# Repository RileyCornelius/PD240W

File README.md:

# PD240W

An adjustable power supply for motor drives using USB-C Power Delivery negotiation, supporting up to **240W at 48V 5A**. This device is designed to be compatible with USB-PD up to 3.2. Firmware runs on a Raspberry Pi Pico ([RP2040](https://www.raspberrypi.com/products/rp2040/)).

> [!NOTE]
> This is a fork of [theohg/PD240W](https://github.com/theohg/PD240W) by Théo Heng. The board, enclosure and firmware build differ from the original. See [Fork Changes](#fork-changes).

Follow the original project's logs and updates on <a href="https://hackaday.io/project/205084-pd240w" target="_blank" title="PD240W on Hackaday.io">
Hackaday.io 
</a>

> [!WARNING]
> **Disclaimer**: Firmware v2.0.0 includes guarded AVS/EPR negotiation, startup restore, and EPR-exit handling, but high-voltage charger interoperability still depends on the source and cable combination you test with. Validate 28V/36V/48V operation on your hardware.

## Table of Contents

- [Fork Changes](#fork-changes)
- [Features](#features)
- [Hardware](#hardware)
- [Quick Start](#quick-start)
- [Controls](#controls)
- [Firmware Structure](#firmware-structure)
- [Want one?](#want-one)
- [Planned Features](#planned-features)
- [Acknowledgements](#acknowledgements)

## Fork Changes

This fork makes these changes to the [original project](https://github.com/theohg/PD240W):

- **5V regulator instead of 17V**: The auxiliary buck regulator (LMR16006X) now outputs 5V instead of the original 17V. Its feedback divider, inductor (now 33µH) and output capacitor (now 22µF 25V) were changed to suit. Firmware v2.1.0 labels the output "5V" and allows it to be enabled when VBUS is 7V or higher (the original required 18V).
- **Top case exposes the whole terminal block**: `casing_top` was modified so the entire output terminal block is uncovered.
- **Enclosure recreated in SolidWorks**: The enclosure is now modeled in SolidWorks, in `mechanical/solidworks/`.
- **Production files for the modified board**: The JLCPCB order files are in `hardware/production/`. The KiBot documentation package in `hardware/Manufacturing/` and the schematic PDF were regenerated for hardware revision 1.1.0. See [hardware/README.md](hardware/README.md#production-files).
- **PlatformIO firmware build**: The firmware builds with PlatformIO from `firmware/` and replaces the original CMake / Pico SDK build. See [Build from Source](#build-from-source).

## Features

- **USB-C Power Delivery**: Negotiates Fixed, PPS (3.3-21V programmable), and AVS (15-48V EPR) profiles
- **Current Limiting**: Adjustable 10mA-5A via INA228 power monitor with hardware overcurrent protection
- **LCD Interface**: 240x320 ST7789 display with anti-aliased fonts and Prusa-style encoder navigation
- **Safety**: Overcurrent ISR, overtemperature monitoring (NTC + INA228)
- **Settings Persistence**: User settings stored in RP2040 flash with CRC32 validation
- **Auto PPS/AVS Tuning**: Closed-loop voltage correction for PPS/AVS charger output accuracy
- **Charger Diagnostics**: On-device PD revision, charger identity, cable inference, and max-power reporting
- **Remote CLI**: USB serial command interface for measurements, PD selection, and settings updates
- **Energy Monitoring**: Tracks mAh delivered since boot via INA228 charge accumulator
- **5V Buck Output**: Optional auxiliary 5V output (17V mock STO/SBC voltage on the original board)
- **Configurable**: Brightness, auto-dim, startup melody, auto-output on boot and more

## Hardware

| Type | Path | Contents |
|------|------|----------|
| PCB (KiCad) | `hardware/` | Schematics and PCB layout |
| PCB (STEP) | `mechanical/PD240W_PCB.stp` | Full PCB 3D model |
| Enclosure (SolidWorks) | `mechanical/solidworks/` | Enclosure assembly and part files |
| Enclosure (STEP) | `mechanical/solidworks/STEP/` | Casing top/bottom, knob, button, LCD support, SWD cover |
| Schematic (PDF) | `hardware/Schematic/` | Schematic for hardware revision 1.1.0 |
| JLCPCB order files | `hardware/production/` | Gerbers zip, BOM, pick and place for JLCPCB |
| Gerbers | `hardware/Manufacturing/Fabrication/` | Gerbers, drill files, ODB++, fabrication drawing |
| BOM | `hardware/Manufacturing/Assembly/` | Bill of materials (CSV, HTML, interactive) |
| Pick & Place | `hardware/Manufacturing/Assembly/` | Pick and place file, assembly drawing |

### Hardware Errata

USB data lines (D+/D-) are reversed in the current PCB revision (1.1.0), preventing native USB communication between the RP2040 and the USB host. This can be easily fixed by crossing the D+ and D- lines on the PCB by crossing the series 27Ω resistors as shown below:

> [!NOTE]
> **TODO**: This fork has not fixed the swapped USB data lines in the PCB layout yet.

## Quick Start

### Flash Pre-built Firmware

1. Download `PD240W.uf2` from the original project's [latest release](https://github.com/theohg/PD240W/releases/latest). This fork has no releases of its own yet.
2. Hold **BOOTSEL** button on the Pico while connecting USB
3. Drag `PD240W.uf2` to the mounted `RPI-RP2` drive

### Build from Source

Requires: [PlatformIO](https://platformio.org/) (CLI, or the VS Code extension recommended in `firmware/.vscode/extensions.json`). On the first build PlatformIO downloads the toolchain and the [Arduino-Pico](https://github.com/earlephilhower/arduino-pico) core, which bundles the Pico SDK.

```bash
git clone https://github.com/RileyCornelius/PD240W.git
cd PD240W/firmware

pio run                  # Debug build (LOG_DEBUG on)
pio run -e pico_release  # Release build (debug logging off, -Werror)
```

The output binary is `firmware/.pio/build/<env>/firmware.uf2`, where `<env>` is `pico` or `pico_release`. Release downloads rename it to `PD240W.uf2`.

The INA228 and TPS26750 drivers are copied into `firmware/lib/` from [ina228_multiplatform](https://github.com/theohg/ina228_multiplatform) and [tps26750_multiplatform](https://github.com/theohg/tps26750_multiplatform). They do not update automatically. To update one, replace its folder in `firmware/lib/` and bump the version in its `library.json` and in `firmware/src/config/version.h`.

### Run Unit Tests

The host tests cover the hardware-free logic headers and run on your PC, not the Pico. They need a host `g++` on `PATH`:

```bash
cd firmware
pio test -e native
```

See [firmware/test/README](firmware/test/README) for details.

### Flash via SWD

```bash
openocd -f interface/cmsis-dap.cfg -f target/rp2040.cfg \
  -c "adapter speed 5000; program firmware/.pio/build/pico/firmware.elf verify reset exit"
```

> [!IMPORTANT]
> **EEPROM Initial Setup**: Before full PD negotiation can work, you must flash the **TPS26750 EEPROM** configuration. This is done via the **EEPROM Flash** workflow found in the **Settings** menu. 
> 
> **Note**: Before the EEPROM is flashed, the board will only power on when connected to a standard 5V non-PD charger (USB BC1.2 mode).

Once the firmware has been successfully flashed, connect the device to a compatible USB-PD power source and interact with the encoder and buttons to navigate the menus and adjust settings as explained below.

> [!NOTE]
> Finding a compact and affordable charger supporting **USB-PD 3.1** (up to 48V EPR) is currently quite rare. Here are a few known options:
>
> | Model | Max single-port PD Output | Voltage Profile | Approx. Price |
> |---|---|---|---|
> | **[UGREEN Nexode 140W](https://fr.ugreen.com/products/ugreen-nexode-140w-chargeur-usb-c-pd-3-1-3-ports)** | 140W | 28V @ 5A | ~60€ |
> | **[Framework Power Adapter - 180W](https://frame.work/fr/fr/products/16-power-adapter?v=FRANCR000F)** | 180W | 36V @ 5A | ~109€ |
> | **[HKY 240W GaN Charger](https://www.amazon.de/-/en/Charger-Framework-Thunderbolt-External-ADP-240KB/dp/B0FLXY1HYW/ref=sr_1_2?crid=3N3IPHZQ5LLC7&dib=eyJ2IjoiMSJ9.Hby-yLg1Ti0JNivqvDzvN57zIH6zG4_c9wlyL50Z52GmOPyP_vKubcMJ3zNZ7RRcIgOo2FKgZio1hprqALfRdOTl2DQ7Dp27o4l66qmaDQw9ctSuX0EaWnDfyVwVAMaSwnUP7h1NBuraYlZnAgiljw.9cbe3P4mLf8D7-0faSCcJpKki5cfrjZLwFO-zW9XlJw&dib_tag=se&keywords=hky+240w&qid=1769454134&sprefix=hky+240w%2Caps%2C102&sr=8-2)** | 240W | 48V @ 5A | ~90€ |
> | **[Framework Power Adapter - 240W](https://frame.work/fr/fr/products/power-adapter-240w?v=FRAKMX000F)** | 240W | 48V @ 5A | ~120€ |
> | **[UGREEN NEXODE 500W](https://eu.ugreen.com/products/ugreen-nexode-500w-6-port-gan-desktop-fast-charger)** | 240W | 48V @ 5A | ~250€ |

## Controls

| Input | Action |
|-------|--------|
| Encoder Rotate | Navigate menus / Adjust values |
| Encoder Click | Confirm / Select |
| BTN1 (top) | Toggle load switch output |
| BTN2 (bottom) | Toggle 5V buck (requires VBUS ≥ 7V) |

### Menu Structure

```mermaid
graph TD
  %% Nodes
      Boot([Boot]) -->|≤2s| Main[Main Screen]
      Main -->|Error| Fault[Fault Screen]
      Fault -->|Click| Main
      
      Main <-->|Click| Menu[Main Menu]

      Menu --> Voltage[Select Voltage]
      Menu --> Current[Current Limit]
      Menu --> Settings[Settings]
      Menu --> AboutFirmware[About PD240W]
      Menu --> AboutCharger[About This Charger]
      Menu --> Back[Back]

      Voltage <-->|Select PDO| AdjV[Adjust Voltage]
      Current <-->|Set Limit| AdjC[Adjust Current]
      
      Settings --> EEPROM[Flash EEPROM]
      Settings --> Configs[Params: Brightness / Sounds / Tuning...]
      AboutFirmware --> Main
      AboutCharger --> Main
      
      %% Styling
      classDef default fill:#f9f9f9,stroke:#333,stroke-width:1px;
      classDef alert fill:#ffcccc,stroke:#cc0000,stroke-width:2px;
      class Fault alert;
```

| Menu Item | Description |
|-----------|-------------|
| Select Voltage | Fixed / PPS / AVS PDO selection |
| Current Limit | 10mA - 5A output current limit adjustment with encoder acceleration |
| Settings | EEPROM flash workflow plus tuning, startup, brightness, and sound options |
| About PD240W | Device identity, firmware build info, flash usage, and project link |
| About This Charger | Live PD revision, CC orientation, QC inference, and cable diagnostics |
| Back | Return to the main live display |

## Firmware Structure

```
firmware/
├── platformio.ini                  Build environments: pico, pico_release, native (tests)
├── lib/
│   ├── ina228_multiplatform/       INA228 power monitor driver
│   └── tps26750_multiplatform/     TPS26750 USB-PD controller driver
├── test/                           Host unit tests (doctest), one folder per suite
└── src/                            Application sources (below)

src/
├── main.cpp                        Entry point, non-blocking main event loop
│
├── hw/
│   ├── hardware.h/cpp              Hardware singleton aggregating all drivers
│   └── interrupts.h/cpp            Centralized GPIO interrupt router (RP2040 single-callback)
│
├── platform/
│   ├── arduino_compat.cpp          Routes the SDK console (printf, getchar) onto the core's UART
│   └── console.h                   Serial console bring-up (logs + CLI)
│
├── cli/                            Serial command interface (see src/cli/README.md)
│
├── config/
│   ├── board_config.h              Pin definitions (Board:: namespace)
│   ├── app_config.h                Timeouts, thresholds, limits (AppConfig:: namespace)
│   └── version.h                   Firmware & hardware version, author...
│
├── drivers/                        Low-level hardware drivers (no business logic)
│   ├── display/
│   │   ├── st7789.h/cpp            SPI LCD driver with AA font rendering
│   │   ├── aa_font.h               Anti-aliased font data structure
│   │   └── font_inter_*.h          Generated Inter font bitmaps (12/14/20/28px)
│   ├── input/
│   │   ├── rotary_enc.h/cpp        Quadrature encoder with velocity tracking
│   │   ├── button.h/cpp            Debounced button with click/long-press
│   │   └── adc_inputs.h/cpp        VBUS voltage + NTC temperature (ADC channels)
│   ├── gpio/                       SimpleIO: digital output with non-blocking blink
│   ├── buzzer/                     PWM buzzer with melody playback
│   └── rgb_led/                    SK6812 via PIO state machine
│
├── logic/                          Application logic
│   ├── state_machine.h/cpp         BOOT -> MAIN <-> MENU <-> ADJUST, FAULT handling
│   ├── safety.h/cpp                Temperature/voltage/current monitoring, fault triggers
│   ├── pd_manager.h/cpp            PD contract caching, PPS keep-alive, auto-tuning
│   ├── settings.h/cpp              Flash persistence with CRC32, debounced saves
│   ├── tps_eeprom_workflow.h/cpp   TPS26750 EEPROM compare/flash state machine
│   ├── cc_controller.h/cpp         Constant-current control via PD voltage requests
│   └── *.h (pure headers)          Host-testable logic: CC regulation, PD diagnostics,
│                                   PPS/AVS tuning, settings storage, thermal monitor
│
├── ui/
│   ├── display_manager.h/cpp       All screen rendering (boot, main, menu, adjust, fault)
│   ├── font_config.h               Central font size mapping (FONT_LARGE/MEDIUM/SMALL)
│   └── assets/pd240w_logo.h        Boot screen logo bitmap
│
├── utils/
│   ├── logging.h                   LOG_INFO/WARN/ERROR/DEBUG/CRITICAL macros
│   ├── pd_voltage.h                Shared programmable-voltage alignment helper
│   ├── tps_eeprom_loader.h/cpp     Low-level TPS26750 EEPROM read/write
│   ├── tps_patch_loader.h/cpp      Pushes the TPS26750 configuration over I2C at boot
│   └── tps26750_patch.c            TPS26750 binary configuration blob
```

## Want one?

Feel free to order assembled PCBs, flash the firmware, and test it for yourself! Manufacturing 5 assembled PCBs will cost approximately **$415**. 

The project is open for contributions. Don't hesitate to improve the code, report bugs, or suggest new features via Pull Requests and Issues!

## License and Copyright

This repository contains different types of source files, which are licensed as follows:

### 1. Hardware files (CC BY-NC 4.0)
All hardware design files in the `hardware/` directory (Schematics, PCB layout, Gerbers, BOM) and the enclosure files in the `mechanical/` directory are licensed under the **Creative Commons Attribution-NonCommercial 4.0 International License**. 

You are free to download, modify, and build this board for personal, educational, and hobbyist use. However, you may **not** use these designs for commercial purposes (such as manufacturing and selling the boards) without prior written permission.

Please see the [LICENSE.txt](./LICENSE.txt) file for full terms.

### 2. Firmware & Software (MIT License)
The firmware and software source code in this repository (the `firmware/` directory) is licensed under the **MIT License**. 

You are free to use, modify, and distribute the software component of this project. 

Please see the [LICENSE-FIRMWARE.txt](./LICENSE-FIRMWARE.txt) file for full terms.

## Planned Features

These are from the original project's roadmap and are not in this fork yet:

- **PPS battery charging in Constant Current (CC) mode**: PPS allows a fixed current mode that can be used for battery charging. This is to be tested by charging lithium-ion battery packs.
- **Improved CLI interface**: Needs more testing and polish.
- **Extended PPS and AVS Range**: Support for PPS voltages as low as 3.5V, AND SPR AVS profiles down to 9V.

## Acknowledgements

PD240W was designed by Théo Heng, who did all of the original hardware design and firmware development as the sole contributor. This fork builds on that work.

The original project was made possible by [Synapticon GmbH](https://www.synapticon.com), who funded and supported its development.

The original project drew inspiration from the work on portable USB-C PD power supplies by CentyLab on the [PocketPD](https://hackaday.io/project/194295-pocketpd-usb-c-portable-bench-power-supply) project and Alex Xia with his [ProtoV MINI](https://hackaday.io/project/204461-protov-mini-tiny-usb-c-breadboard-power-supply).

***

Originally made with ❤️ by Théo Heng. Fork maintained by Riley Cornelius.

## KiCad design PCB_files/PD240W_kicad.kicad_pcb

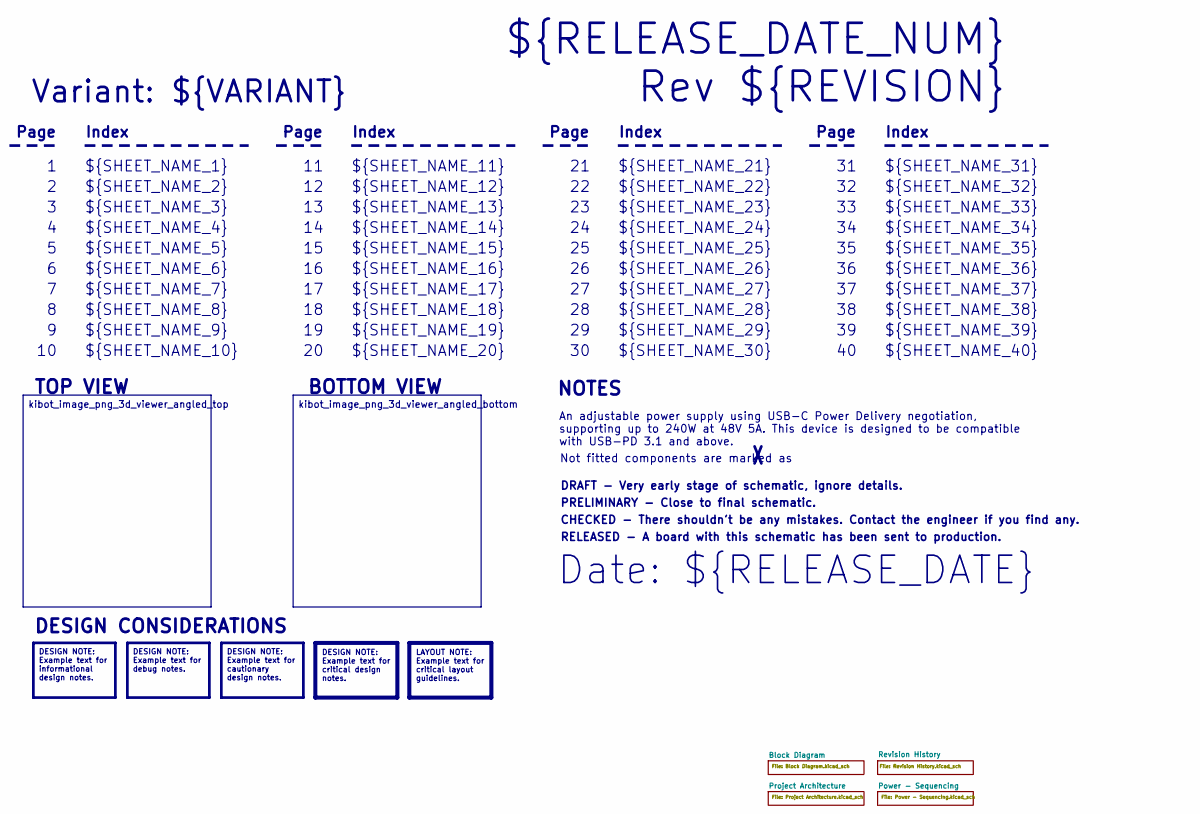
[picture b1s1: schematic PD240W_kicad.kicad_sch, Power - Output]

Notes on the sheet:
Variant: ${VARIANT}
RELEASED - A board with this schematic has been sent to production.
${SHEET_NAME_24}
Index
Page
PRELIMINARY - Close to final schematic.
${SHEET_NAME_22}
DRAFT - Very early stage of schematic, ignore details.
${SHEET_NAME_12}
${SHEET_NAME_8}
${SHEET_NAME_2}
${SHEET_NAME_5}
${SHEET_NAME_20}
${SHEET_NAME_23}
${RELEASE_DATE_NUM}
${SHEET_NAME_35}
Not fitted components are marked as
${SHEET_NAME_11}
${SHEET_NAME_6}
${SHEET_NAME_37}
${SHEET_NAME_26}
${SHEET_NAME_36}
Rev ${REVISION}
${SHEET_NAME_15}
CHECKED - There shouldn't be any mistakes. Contact the engineer if you find any.
BOTTOM VIEW
${SHEET_NAME_14}
${SHEET_NAME_21}
${SHEET_NAME_17}
${SHEET_NAME_18}
Date: ${RELEASE_DATE}
${SHEET_NAME_7}
${SHEET_NAME_31}
NOTES
${SHEET_NAME_40}
${SHEET_NAME_39}
${SHEET_NAME_32}
${SHEET_NAME_1}
${SHEET_NAME_9}
${SHEET_NAME_38}

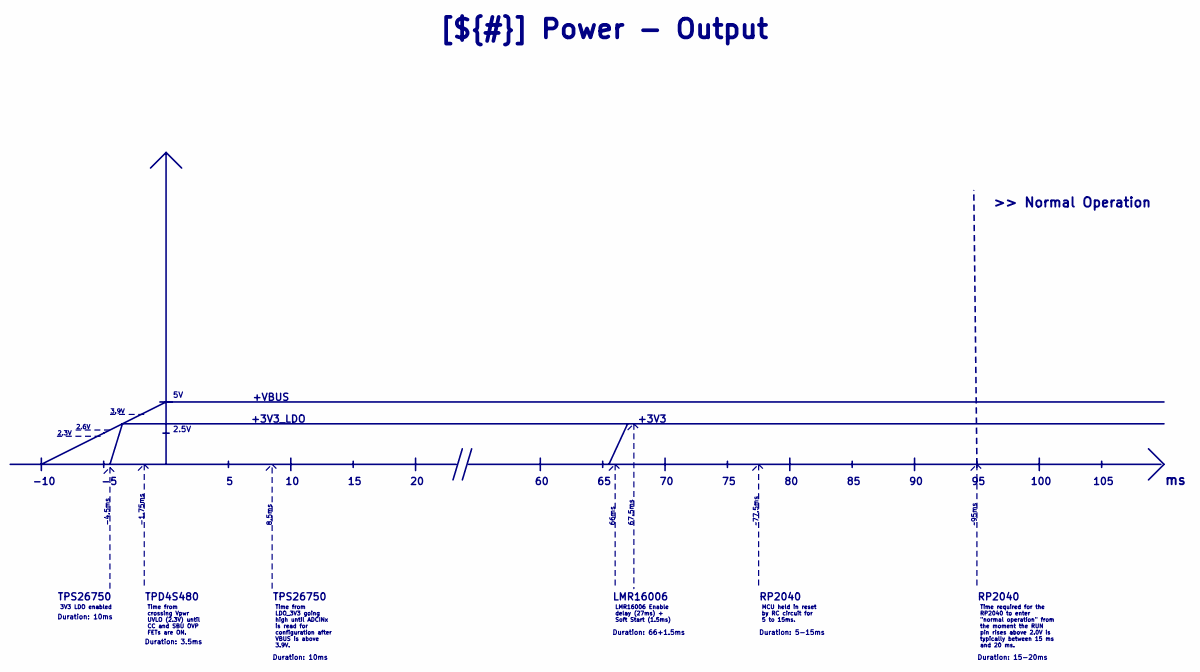
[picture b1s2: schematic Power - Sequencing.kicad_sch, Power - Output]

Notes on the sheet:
~95ms
-1.75ms
2.5V
3.9V
Duration: 15-20ms
RP2040
TPS26750
LMR16006
2.6V
+VBUS
Duration: 10ms
100
Duration: 3.5ms
Duration: 66+1.5ms
8.5ms
+3V3_LDO
66ms
67.5ms
Duration: 5-15ms
2.3V
105
~77.5ms
TPD4S480
+3V3
>> Normal Operation
-4.5ms
-10
3V3 LDO enabled
Time from LDO_3V3 going high until ADCINx is read for configuration after VBUS is above 3.9V.
Time from crossing Vpwr UVLO (2.3V) until CC and SBU OVP FETs are ON.
Time required for the RP2040 to enter "normal operation" from the moment the RUN pin rises above 2.0V is typically between 15 ms and 20 ms.
[${#}] ${TITLE}
MCU held in reset by RC circuit for 5 to 15ms.
LMR16006 Enable delay (27ms) + Soft Start (1.5ms)

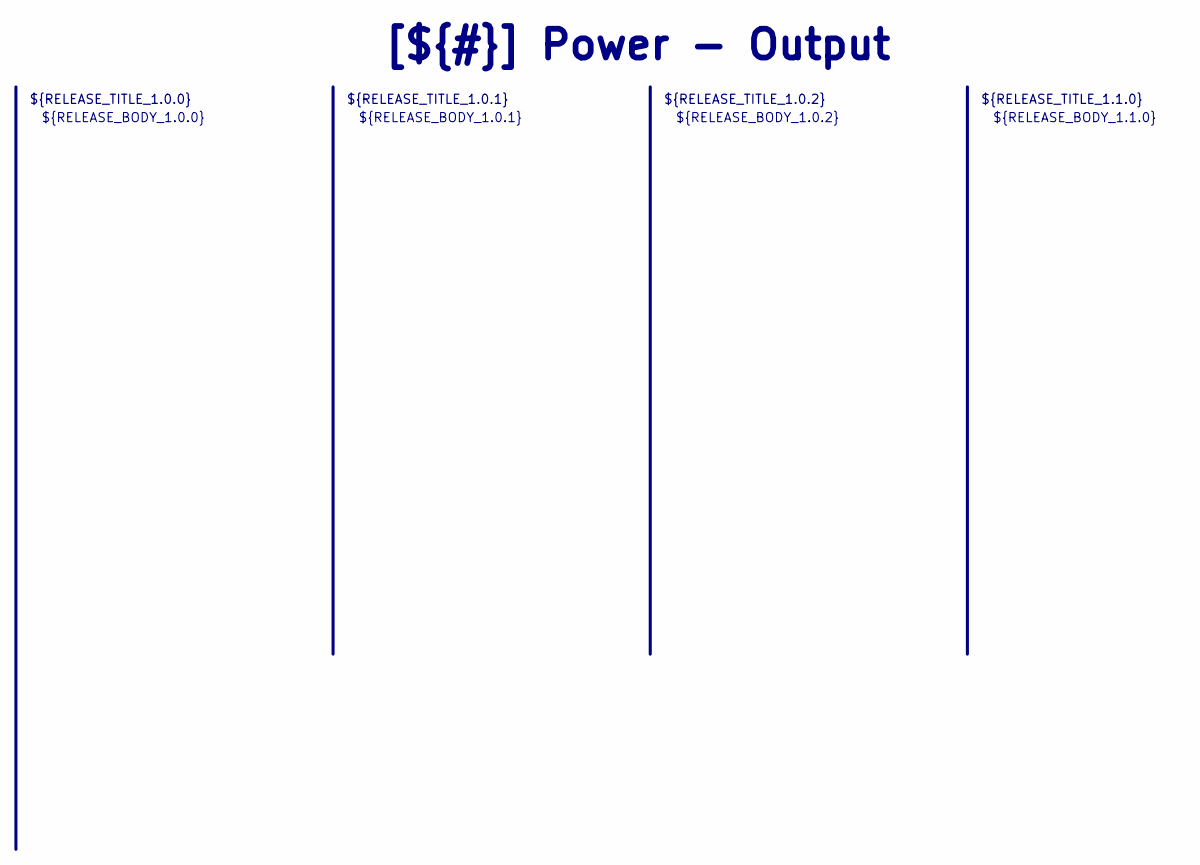
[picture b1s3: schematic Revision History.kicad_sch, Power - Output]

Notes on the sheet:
${RELEASE_BODY_1.1.0}
[${#}] ${TITLE}
${RELEASE_BODY_1.0.0}
${RELEASE_TITLE_1.0.2}
${RELEASE_BODY_1.0.2}
${RELEASE_BODY_1.0.1}
${RELEASE_TITLE_1.0.0}
${RELEASE_TITLE_1.0.1}
${RELEASE_TITLE_1.1.0}

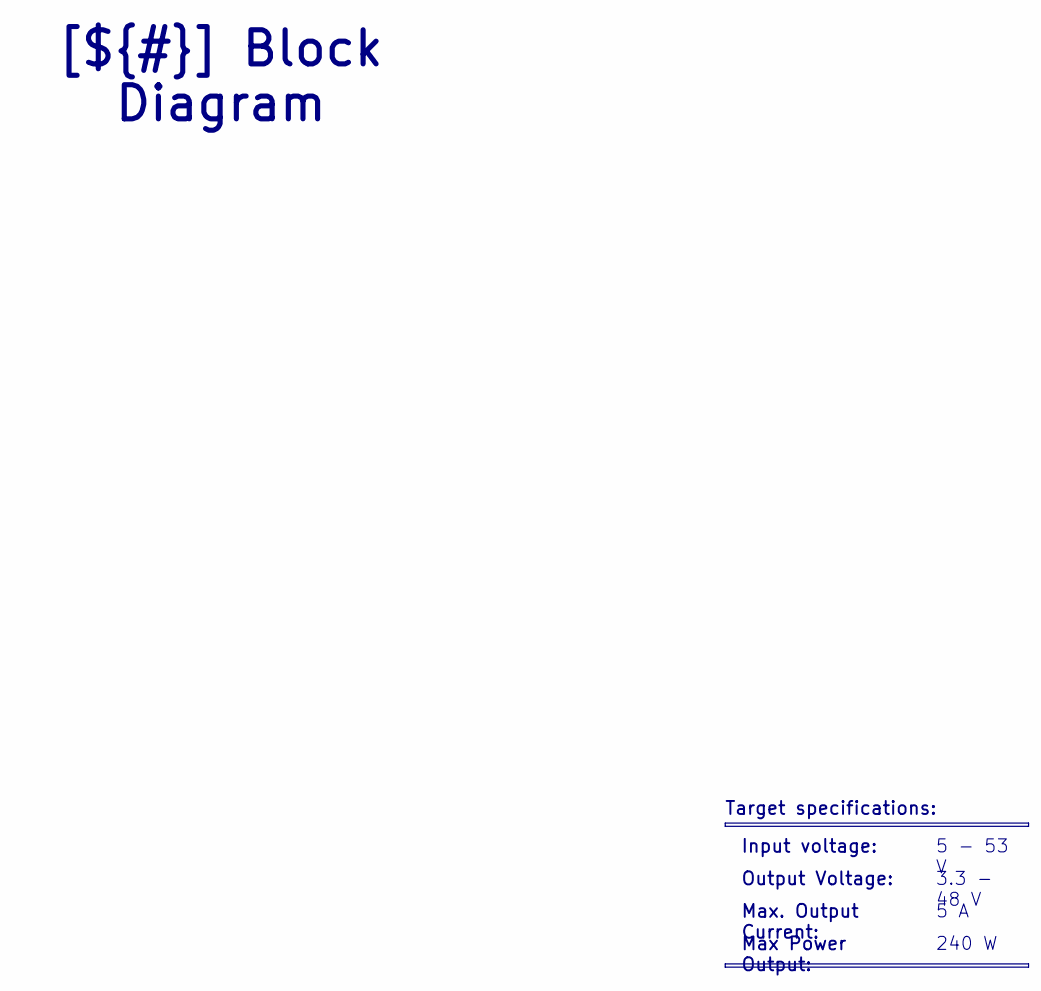
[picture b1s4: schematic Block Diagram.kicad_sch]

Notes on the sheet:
Max Power Output:
5 - 53 V
240 W
[${#}] ${TITLE}
3.3 - 48 V
Input voltage:
Target specifications:
Max. Output Current:
5 A
Output Voltage:

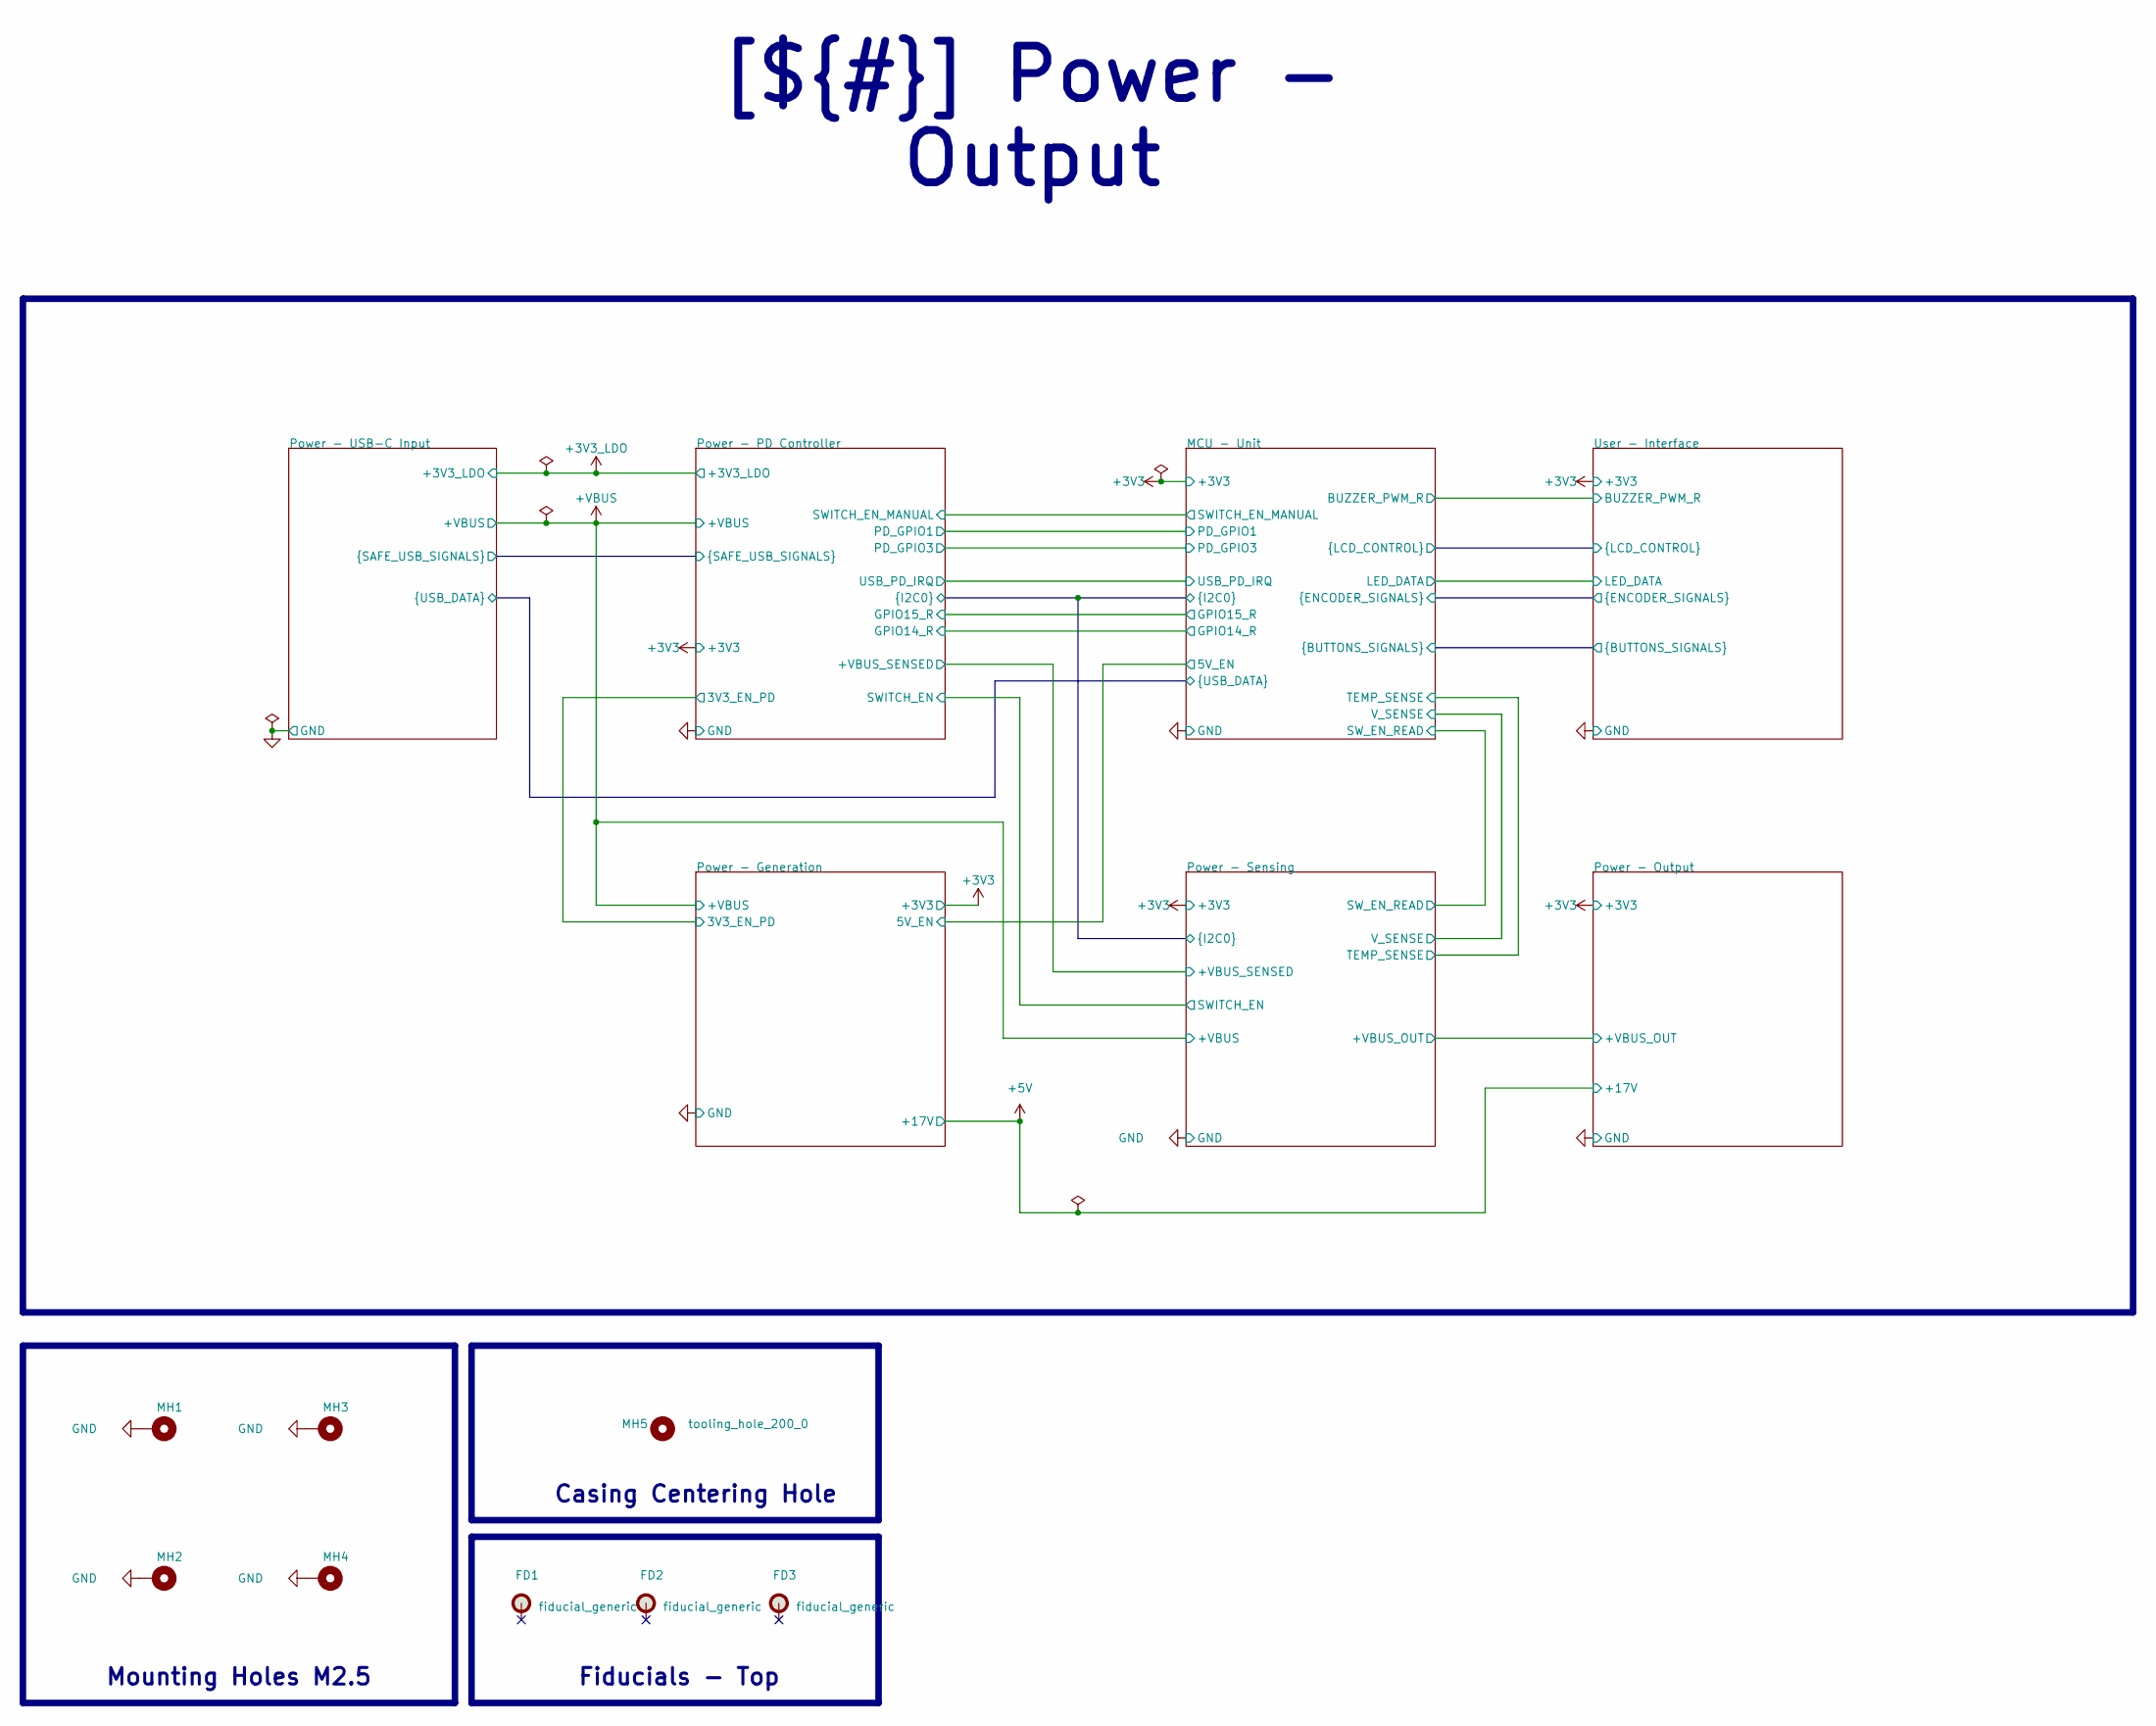
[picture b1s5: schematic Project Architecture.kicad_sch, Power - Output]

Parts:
FD1, FD2, FD3: fiducial_generic; fiducial_round_130
MH1, MH2, MH3, MH4: mounting_hole_270_540_p_via_8_50; MountingHole_2.7mm_M2.5_Pad_Via
MH5: tooling_hole_200_0; tooling_hole_200_0_np

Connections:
GND: MH1.1 (1_1), MH2.1 (1_1), MH3.1 (1_1), MH4.1 (1_1); also elsewhere on the board

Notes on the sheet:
Mounting Holes M2.5
Casing Centering Hole
Fiducials - Top
[${#}] ${TITLE}

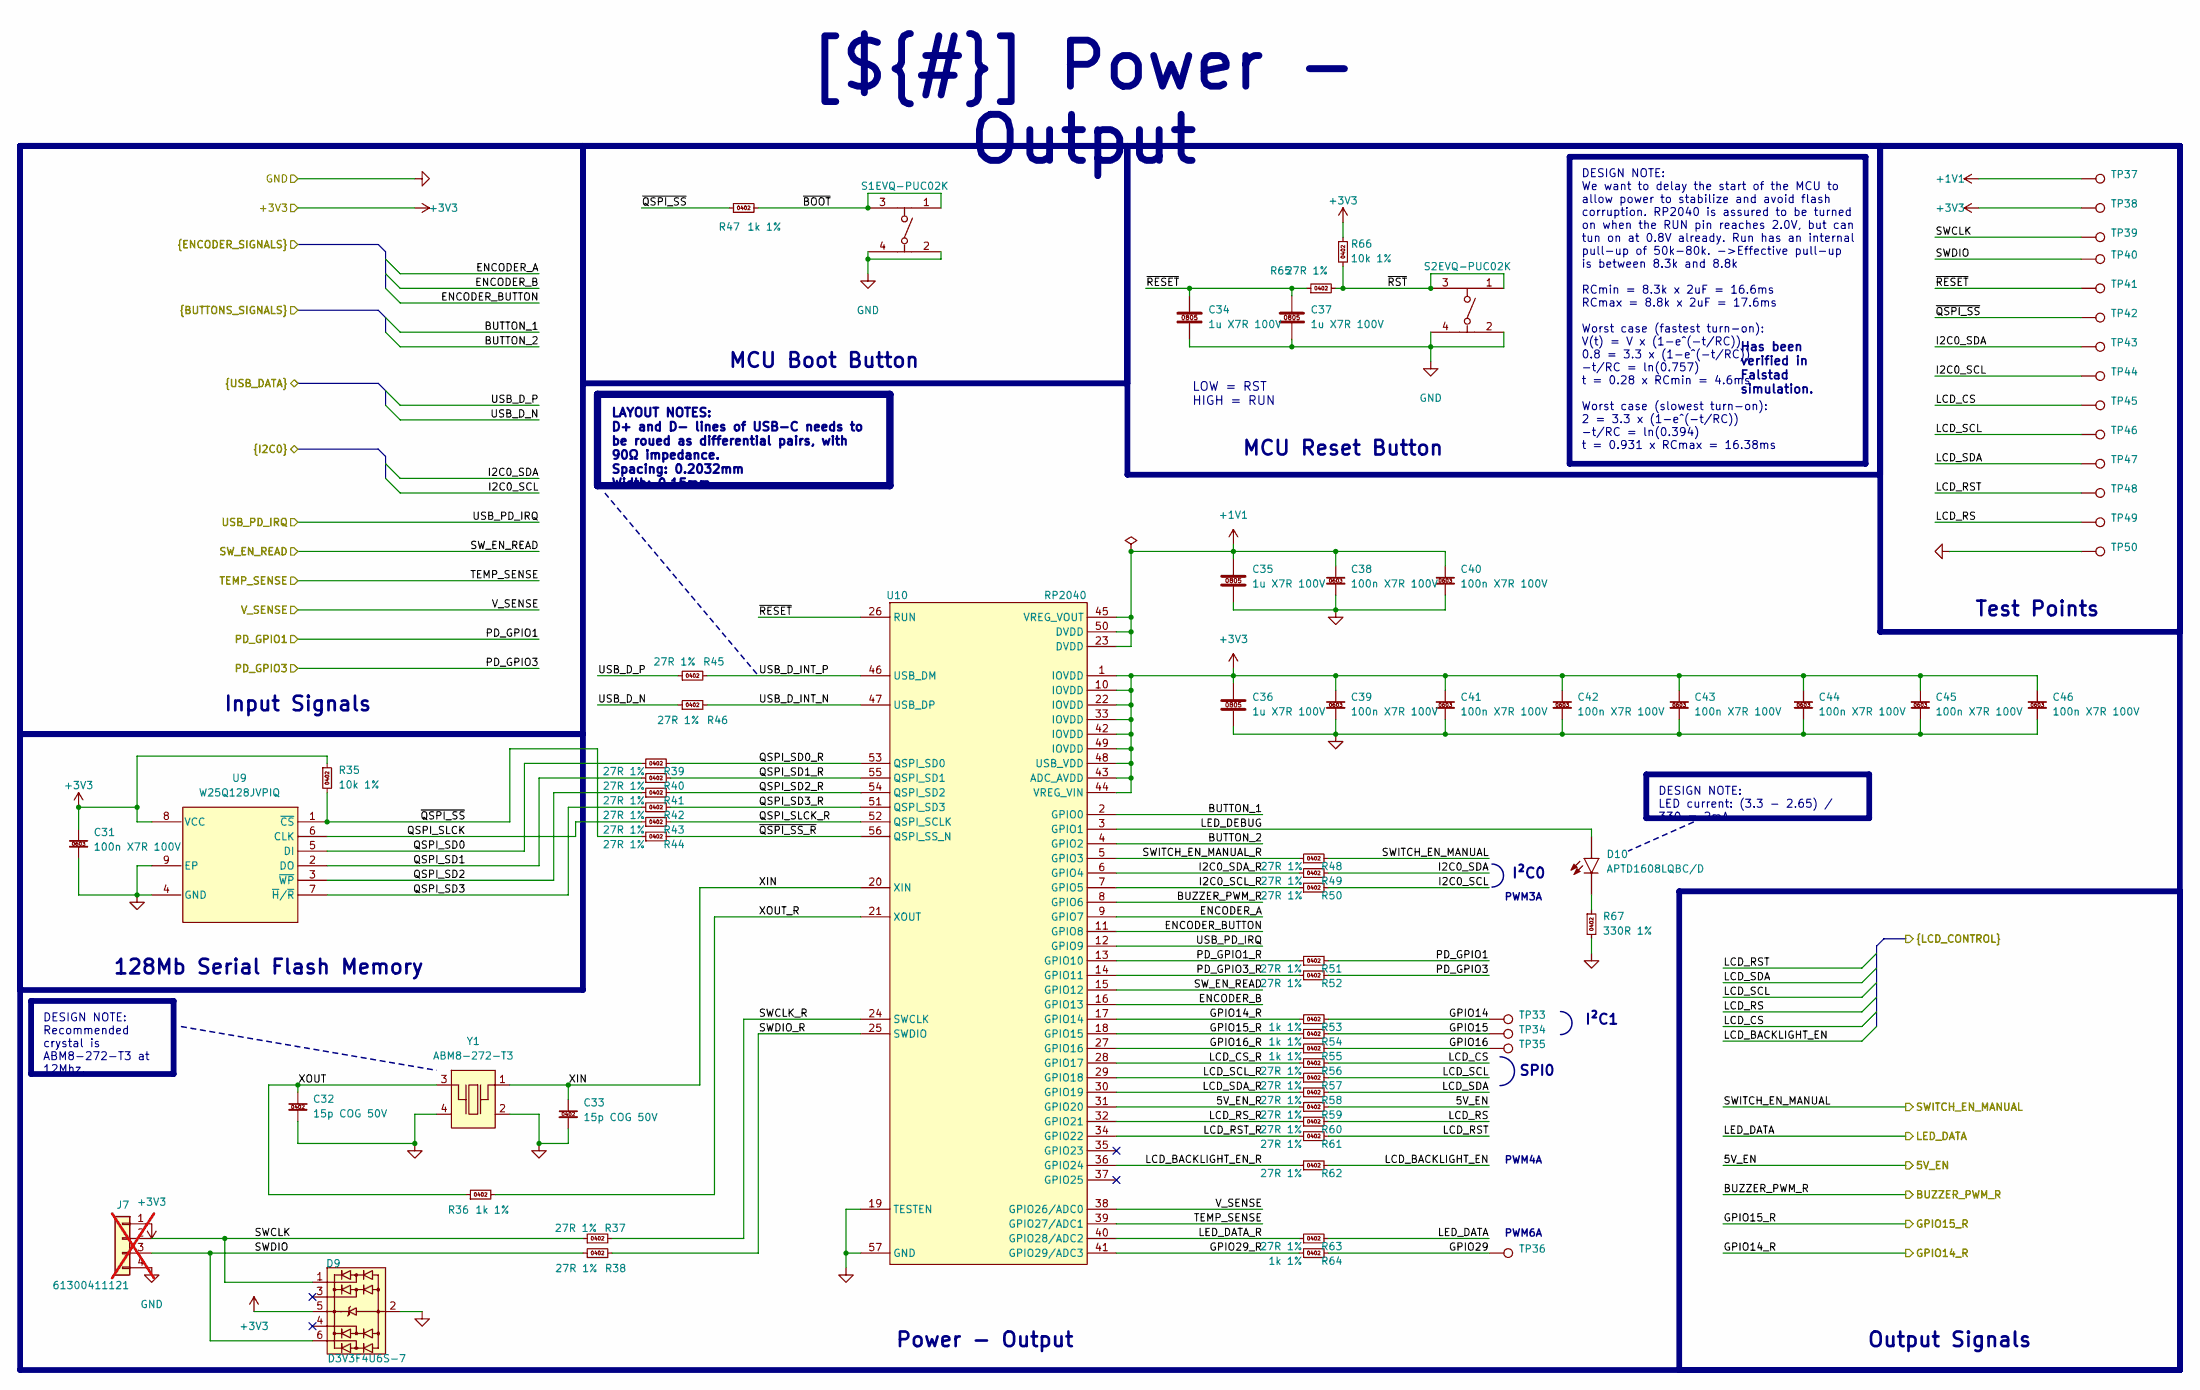
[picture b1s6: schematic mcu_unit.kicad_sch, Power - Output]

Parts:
C31, C38, C39, C40, C41, C42, C43, C44, C45, C46: 100n X7R 100V; capc_1608_09_l; MFR Part # CL10B104KC8NNNC; LCSC C15725
C32, C33: 15p COG 50V; capc_1005_06_n; MFR Part # 0402CG150J500NT; LCSC C1548
C34, C35, C36, C37: 1u X7R 100V; capc_2012_14_n; MFR Part # CC0805KKX7R0BB105; LCSC C5370002
D9: D3V3F4U6S-7; sot363_sc88_65p_200x125x110_n; MFR Part # D3V3F4U6S-7; LCSC C1869321
D10: APTD1608LQBC/D; kingbright_0603_blue; MFR Part # APTD1608LQBC/D; LCSC C5344742
J7: 61300411121; we_61300411121; MFR Part # 61300411121; LCSC C5184785; not fitted
R35, R66: 10k 1%; resc_1005_04_n; MFR Part # 0402WGF1002TCE; LCSC C25744
R36, R47, R53, R54, R55, R64: 1k 1%; resc_1005_04_m; MFR Part # 0402WGF1001TCE; LCSC C11702
R37, R38, R39, R40, R41, R42, R43, R44, R45, R46, R48, R49, R50, R51, R52, R56, R57, R58, R59, R60, R61, R62, R63, R65: 27R 1%; resc_1005_04_m; MFR Part # RC0402FR-0727RL; LCSC C138021
R67: 330R 1%; resc_1005_04_m; MFR Part # 0402WGF3300TCE; LCSC C25104
S1, S2: EVQ-PUC02K; EVQPUC02K; MFR Part # EVQ-PUC02K; LCSC C79174
TP33, TP34, TP35, TP36, TP50: sp_oval_300x100
TP37, TP38, TP39, TP40, TP41, TP42, TP43, TP44, TP45, TP46, TP47, TP48, TP49: tp_round_70
U9: W25Q128JVPIQ; wson8_127p_600x500x80_tp_435x340_n; MFR Part # W25Q128JVPIQ; LCSC C190862
U10: RP2040; qfn56_40p_700x700x90_tp_320x320_mfg; MFR Part # SC0914(13); LCSC C2040
Y1: ABM8-272-T3; osccc_320x205x80_abm8; MFR Part # ABM8-272-T3; LCSC C20625731

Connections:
+1V1: C35.1, C38.1, C40.1, TP37.1 (1_1), U10.23 (DVDD), U10.45 (VREG_VOUT), U10.50 (DVDD)
+3V3: C31.1, C36.1, C39.1, C41.1, C42.1, C43.1, C44.1, C45.1, C46.1, D9.5, J7.1, R35.1, R66.1, TP38.1 (1_1), U9.8 (VCC), U10.1 (IOVDD), U10.10 (IOVDD), U10.22 (IOVDD), U10.33 (IOVDD), U10.42 (IOVDD), U10.43 (ADC_AVDD), U10.44 (VREG_VIN), U10.48 (USB_VDD), U10.49 (IOVDD); also elsewhere on the board
/Project Architecture/MCU - Unit/5V_EN: R59.2; also elsewhere on the board
/Project Architecture/MCU - Unit/5V_EN_R: R59.1, U10.31 (GPIO20)
/Project Architecture/MCU - Unit/BUTTON_1: U10.2 (GPIO0); also elsewhere on the board
/Project Architecture/MCU - Unit/BUTTON_2: U10.4 (GPIO2); also elsewhere on the board
/Project Architecture/MCU - Unit/BUZZER_PWM_R: U10.8 (GPIO6); also elsewhere on the board
/Project Architecture/MCU - Unit/ENCODER_A: U10.9 (GPIO7); also elsewhere on the board
/Project Architecture/MCU - Unit/ENCODER_B: U10.16 (GPIO13); also elsewhere on the board
/Project Architecture/MCU - Unit/ENCODER_BUTTON: U10.11 (GPIO8); also elsewhere on the board
/Project Architecture/MCU - Unit/GPIO14: R53.2, TP33.1 (1_1)
/Project Architecture/MCU - Unit/GPIO14_R: R53.1, U10.17 (GPIO14); also elsewhere on the board
/Project Architecture/MCU - Unit/GPIO15: R54.2, TP34.1 (1_1)
/Project Architecture/MCU - Unit/GPIO15_R: R54.1, U10.18 (GPIO15); also elsewhere on the board
/Project Architecture/MCU - Unit/GPIO16: R55.2, TP35.1 (1_1)
/Project Architecture/MCU - Unit/GPIO16_R: R55.1, U10.27 (GPIO16)
/Project Architecture/MCU - Unit/GPIO29: R64.2, TP36.1 (1_1)
/Project Architecture/MCU - Unit/GPIO29_R: R64.1, U10.41 (GPIO29/ADC3)
/Project Architecture/MCU - Unit/I2C0_SCL: R50.2, TP44.1 (1_1); also elsewhere on the board
/Project Architecture/MCU - Unit/I2C0_SCL_R: R50.1, U10.7 (GPIO5)
/Project Architecture/MCU - Unit/I2C0_SDA: R49.2, TP43.1 (1_1); also elsewhere on the board
/Project Architecture/MCU - Unit/I2C0_SDA_R: R49.1, U10.6 (GPIO4)
/Project Architecture/MCU - Unit/LCD_BACKLIGHT_EN: R62.2; also elsewhere on the board
/Project Architecture/MCU - Unit/LCD_BACKLIGHT_EN_R: R62.1, U10.36 (GPIO24)
/Project Architecture/MCU - Unit/LCD_CS: R56.2, TP45.1 (1_1); also elsewhere on the board
/Project Architecture/MCU - Unit/LCD_CS_R: R56.1, U10.28 (GPIO17)
/Project Architecture/MCU - Unit/LCD_RS: R60.2, TP49.1 (1_1); also elsewhere on the board
/Project Architecture/MCU - Unit/LCD_RST: R61.2, TP48.1 (1_1); also elsewhere on the board
/Project Architecture/MCU - Unit/LCD_RST_R: R61.1, U10.34 (GPIO22)
/Project Architecture/MCU - Unit/LCD_RS_R: R60.1, U10.32 (GPIO21)
/Project Architecture/MCU - Unit/LCD_SCL: R57.2, TP46.1 (1_1); also elsewhere on the board
/Project Architecture/MCU - Unit/LCD_SCL_R: R57.1, U10.29 (GPIO18)
/Project Architecture/MCU - Unit/LCD_SDA: R58.2, TP47.1 (1_1); also elsewhere on the board
/Project Architecture/MCU - Unit/LCD_SDA_R: R58.1, U10.30 (GPIO19)
/Project Architecture/MCU - Unit/LED_DATA: R63.2; also elsewhere on the board
/Project Architecture/MCU - Unit/LED_DATA_R: R63.1, U10.40 (GPIO28/ADC2)
/Project Architecture/MCU - Unit/LED_DEBUG: D10.2 (A), U10.3 (GPIO1)
/Project Architecture/MCU - Unit/PD_GPIO1: R51.2; also elsewhere on the board
/Project Architecture/MCU - Unit/PD_GPIO1_R: R51.1, U10.13 (GPIO10)
/Project Architecture/MCU - Unit/PD_GPIO3: R52.2; also elsewhere on the board
/Project Architecture/MCU - Unit/PD_GPIO3_R: R52.1, U10.14 (GPIO11)
/Project Architecture/MCU - Unit/QSPI_SD0: R39.1, U9.5 (DI)
/Project Architecture/MCU - Unit/QSPI_SD0_R: R39.2, U10.53 (QSPI_SD0)
/Project Architecture/MCU - Unit/QSPI_SD1: R40.1, U9.2 (DO)
/Project Architecture/MCU - Unit/QSPI_SD1_R: R40.2, U10.55 (QSPI_SD1)
/Project Architecture/MCU - Unit/QSPI_SD2: R41.1, U9.3 (~WP)
/Project Architecture/MCU - Unit/QSPI_SD2_R: R41.2, U10.54 (QSPI_SD2)
/Project Architecture/MCU - Unit/QSPI_SD3: R42.1, U9.7 (~H/~R)
/Project Architecture/MCU - Unit/QSPI_SD3_R: R42.2, U10.51 (QSPI_SD3)
/Project Architecture/MCU - Unit/QSPI_SLCK: R43.1, U9.6 (CLK)
/Project Architecture/MCU - Unit/QSPI_SLCK_R: R43.2, U10.52 (QSPI_SCLK)
/Project Architecture/MCU - Unit/SWCLK: D9.1, J7.2, R37.1, TP39.1 (1_1)
/Project Architecture/MCU - Unit/SWCLK_R: R37.2, U10.24 (SWCLK)
/Project Architecture/MCU - Unit/SWDIO: D9.6, J7.3, R38.1, TP40.1 (1_1)
/Project Architecture/MCU - Unit/SWDIO_R: R38.2, U10.25 (SWDIO)
/Project Architecture/MCU - Unit/SWITCH_EN_MANUAL: R48.2; also elsewhere on the board
/Project Architecture/MCU - Unit/SWITCH_EN_MANUAL_R: R48.1, U10.5 (GPIO3)
/Project Architecture/MCU - Unit/SW_EN_READ: U10.15 (GPIO12); also elsewhere on the board
/Project Architecture/MCU - Unit/TEMP_SENSE: U10.39 (GPIO27/ADC1); also elsewhere on the board
/Project Architecture/MCU - Unit/USB_D_INT_N: R46.2, U10.47 (USB_DP)
/Project Architecture/MCU - Unit/USB_D_INT_P: R45.2, U10.46 (USB_DM)
/Project Architecture/MCU - Unit/USB_D_N: R46.1; also elsewhere on the board
/Project Architecture/MCU - Unit/USB_D_P: R45.1; also elsewhere on the board
/Project Architecture/MCU - Unit/USB_PD_IRQ: U10.12 (GPIO9); also elsewhere on the board
/Project Architecture/MCU - Unit/V_SENSE: U10.38 (GPIO26/ADC0); also elsewhere on the board
/Project Architecture/MCU - Unit/XIN: C33.1, U10.20 (XIN), Y1.1
/Project Architecture/MCU - Unit/XOUT: C32.1, R36.1, Y1.3
/Project Architecture/MCU - Unit/XOUT_R: R36.2, U10.21 (XOUT)
/Project Architecture/MCU - Unit/~BOOT: R47.2, S1.1, S1.3
/Project Architecture/MCU - Unit/~QSPI_SS_R: R44.2, U10.56 (QSPI_SS_N)
/Project Architecture/MCU - Unit/~QSPI_SS: R35.2, R44.1, R47.1, TP42.1 (1_1), U9.1 (~CS)
/Project Architecture/MCU - Unit/~RESET: C34.1, C37.1, R65.1, TP41.1 (1_1), U10.26 (RUN)
/Project Architecture/MCU - Unit/~RST: R65.2, R66.2, S2.1, S2.3
GND: C31.2, C32.2, C33.2, C34.2, C35.2, C36.2, C37.2, C38.2, C39.2, C40.2, C41.2, C42.2, C43.2, C44.2, C45.2, C46.2, D9.2, J7.4, R67.2, S1.2, S1.4, S2.2, S2.4, TP50.1 (1_1), U9.4 (GND), U9.9 (EP), U10.19 (TESTEN), U10.57 (GND), Y1.2, Y1.4; also elsewhere on the board
unnamed: D10.1 (C), R67.1

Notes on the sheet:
PWM4A
MCU Boot Button
MCU Reset Button
Input Signals
128Mb Serial Flash Memory
Test Points
I²C1
Output Signals
SPI0
I²C0
PWM6A
${TITLE}
PWM3A
LOW = RST HIGH = RUN
LAYOUT NOTES: D+ and D- lines of USB-C needs to be roued as differential pairs, with 90Ω impedance. Spacing: 0.2032mm Width: 0.15mm
DESIGN NOTE: We want to delay the start of the MCU to allow power to stabilize and avoid flash corruption. RP2040 is assured to be turned on when the RUN pin reaches 2.0V, but can tun on at 0.8V already. Run has an internal pull-up of 50k-80k. ->Effective pull-up is between 8.3k and 8.8k RCmin = 8.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
DESIGN NOTE: Recommended crystal is ABM8-272-T3 at 12Mhz.
Has been verified in Falstad simulation.
DESIGN NOTE: LED current: (3.3 - 2.65) / 330 = 2mA
[${#}] ${TITLE}
